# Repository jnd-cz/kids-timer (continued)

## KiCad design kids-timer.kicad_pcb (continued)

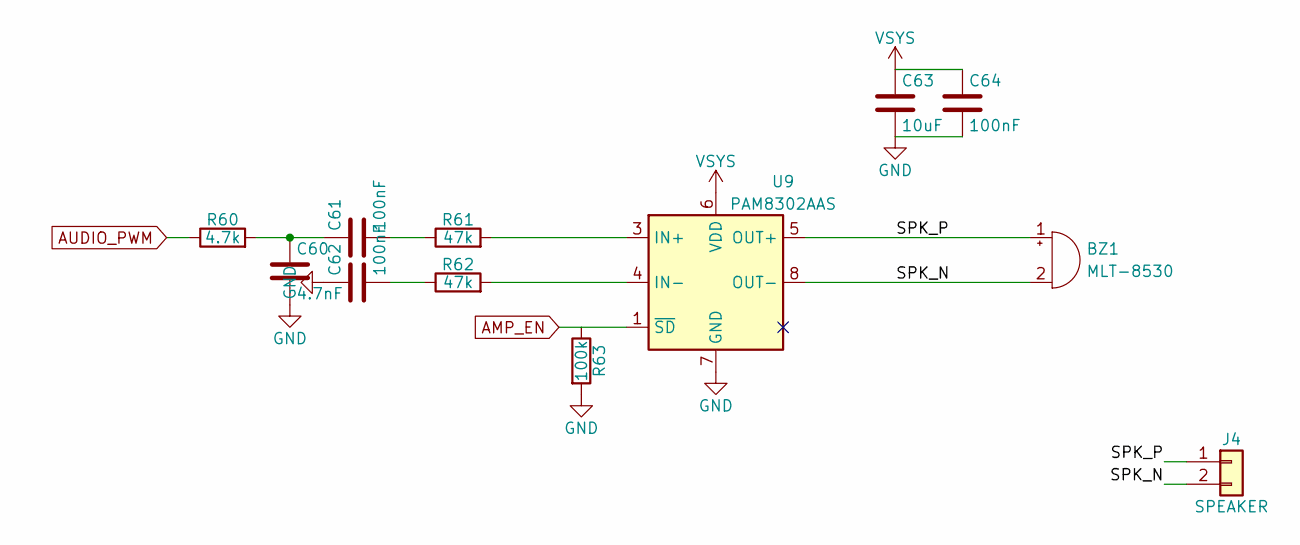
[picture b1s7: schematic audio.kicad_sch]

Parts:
BZ1: MLT-8530; Buzzer_HNDZ_MLT-8530_8.5x8.5mm; MPN MLT-8530; LCSC C94599
C60: 4.7nF; C_0402_1005Metric; LCSC C1538
C61, C62, C64: 100nF; C_0402_1005Metric; LCSC C1525
C63: 10uF; C_0805_2012Metric; LCSC C15850
J4: SPEAKER; JST_PH_S2B-PH-SM4-TB_1x02-1MP_P2.00mm_Horizontal; MPN S2B-PH-SM4-TB(LF)(SN); LCSC C295747
R60: 4.7k; R_0402_1005Metric; LCSC C25900
R61, R62: 47k; R_0402_1005Metric; LCSC C25792
R63: 100k; R_0402_1005Metric; LCSC C25741
U9: PAM8302AAS; MSOP-8_3x3mm_P0.65mm; MPN PAM8302AASCR; LCSC C113367

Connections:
/Audio/SPK_N: BZ1.2 (-), J4.2, U9.8 (OUT-)
/Audio/SPK_P: BZ1.1 (+), J4.1, U9.5 (OUT+)
AMP_EN: R63.1, U9.1 (~SD); also elsewhere on the board
AUDIO_PWM: R60.1; also elsewhere on the board
unnamed: C60.1, C61.1, R60.2
unnamed: C61.2, R61.1
unnamed: C62.2, R62.1
unnamed: R61.2, U9.3 (IN+)
unnamed: R62.2, U9.4 (IN-)
VSYS: C63.1, C64.1, U9.6 (VDD); also elsewhere on the board

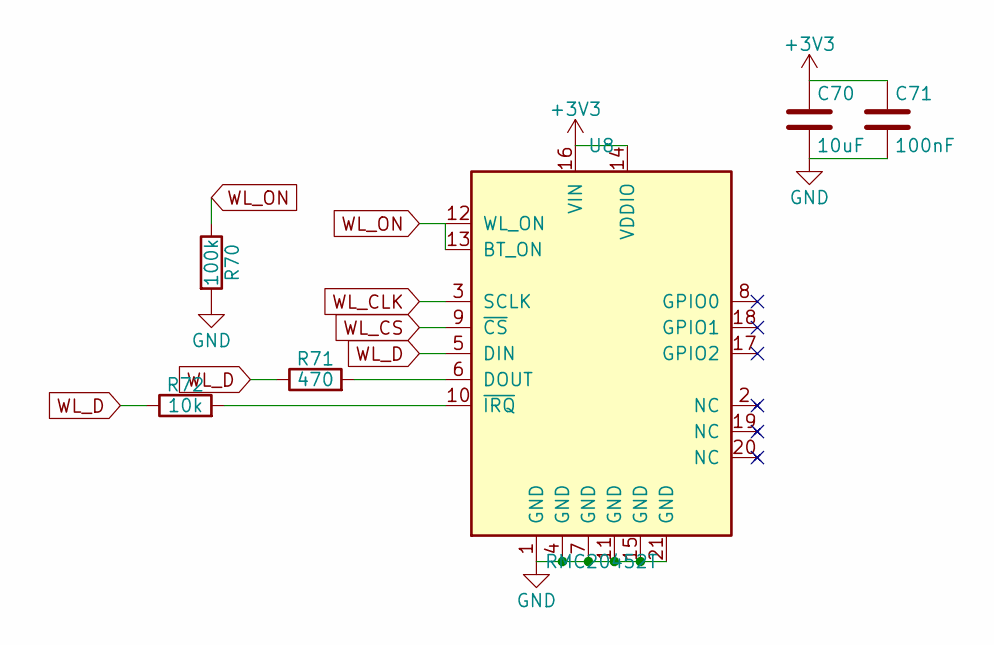
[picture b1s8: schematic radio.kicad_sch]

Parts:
C70: 10uF; C_0805_2012Metric; LCSC C15850
C71: 100nF; C_0402_1005Metric; LCSC C1525
R70: 100k; R_0402_1005Metric; LCSC C25741
R71: 470; R_0402_1005Metric; LCSC C25117
R72: 10k; R_0402_1005Metric; LCSC C25744
U8: RMC20452T; RaspberryPi_RM2_14.5x16.5mm; MPN RMC20452T; LCSC C49451547

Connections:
+3V3: C70.1, C71.1, U8.14 (VDDIO), U8.16 (VIN); also elsewhere on the board
unnamed: R71.2, U8.6 (DOUT)
unnamed: R72.2, U8.10 (~IRQ)
WL_CLK: U8.3 (SCLK); also elsewhere on the board
WL_CS: U8.9 (~CS); also elsewhere on the board
WL_D: R71.1, R72.1, U8.5 (DIN); also elsewhere on the board
WL_ON: R70.1, U8.12 (WL_ON), U8.13 (BT_ON); also elsewhere on the board

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
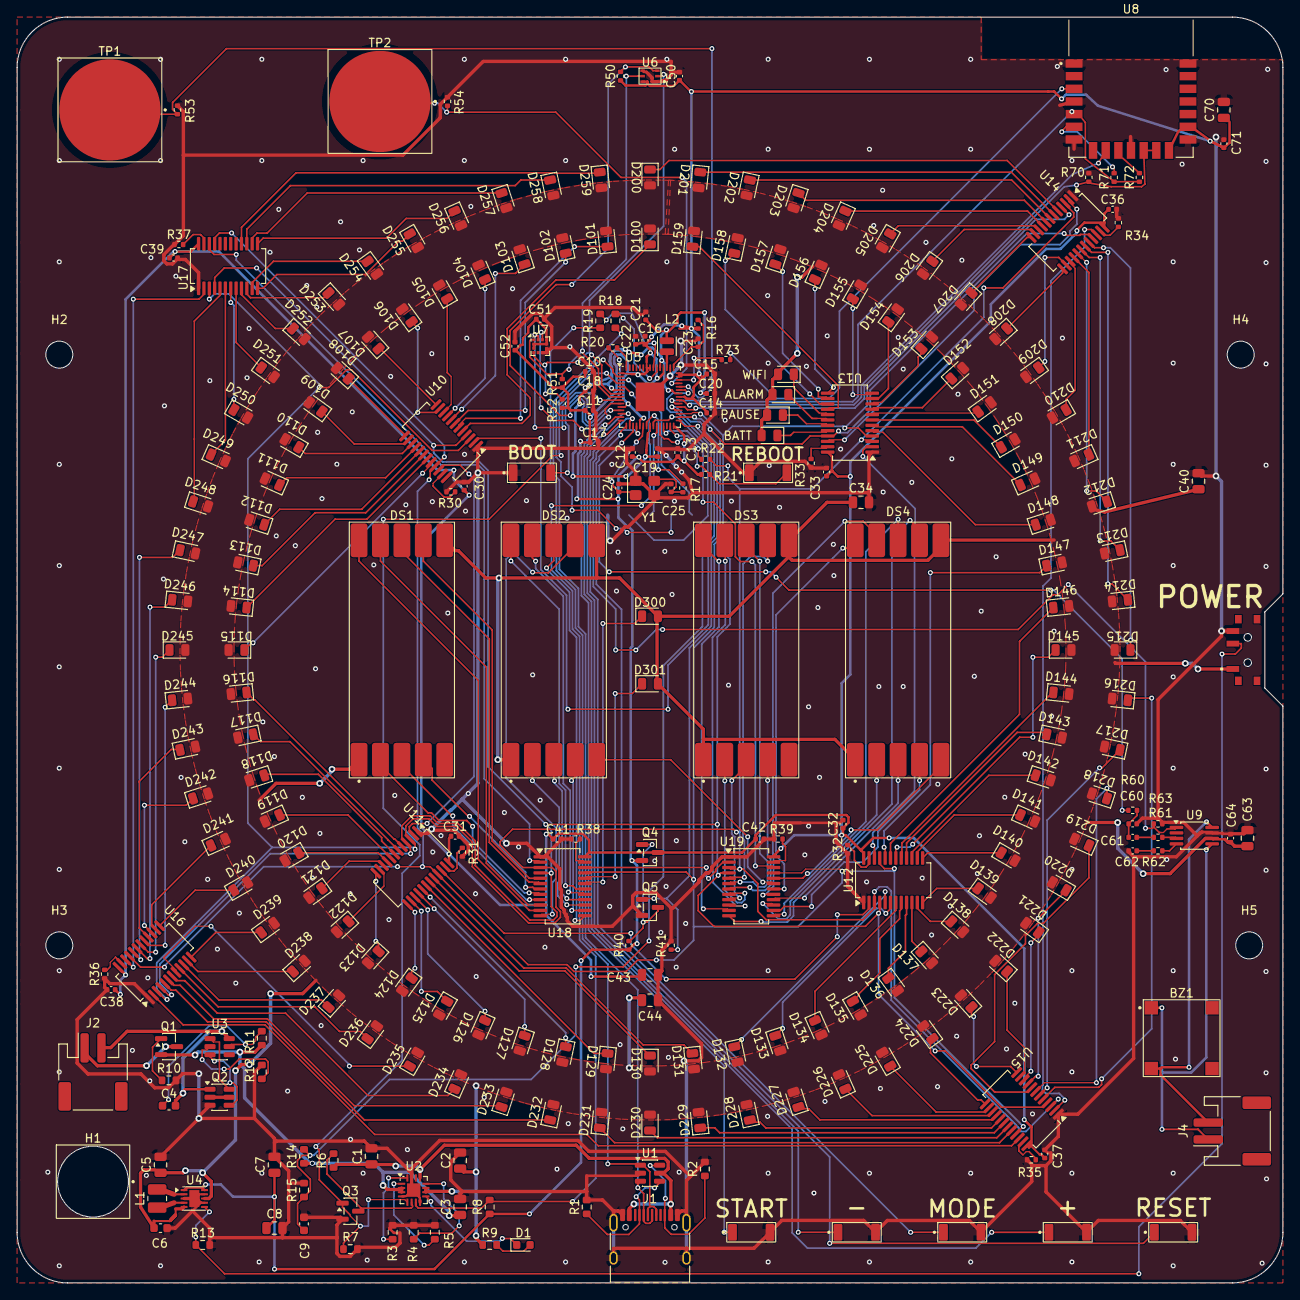
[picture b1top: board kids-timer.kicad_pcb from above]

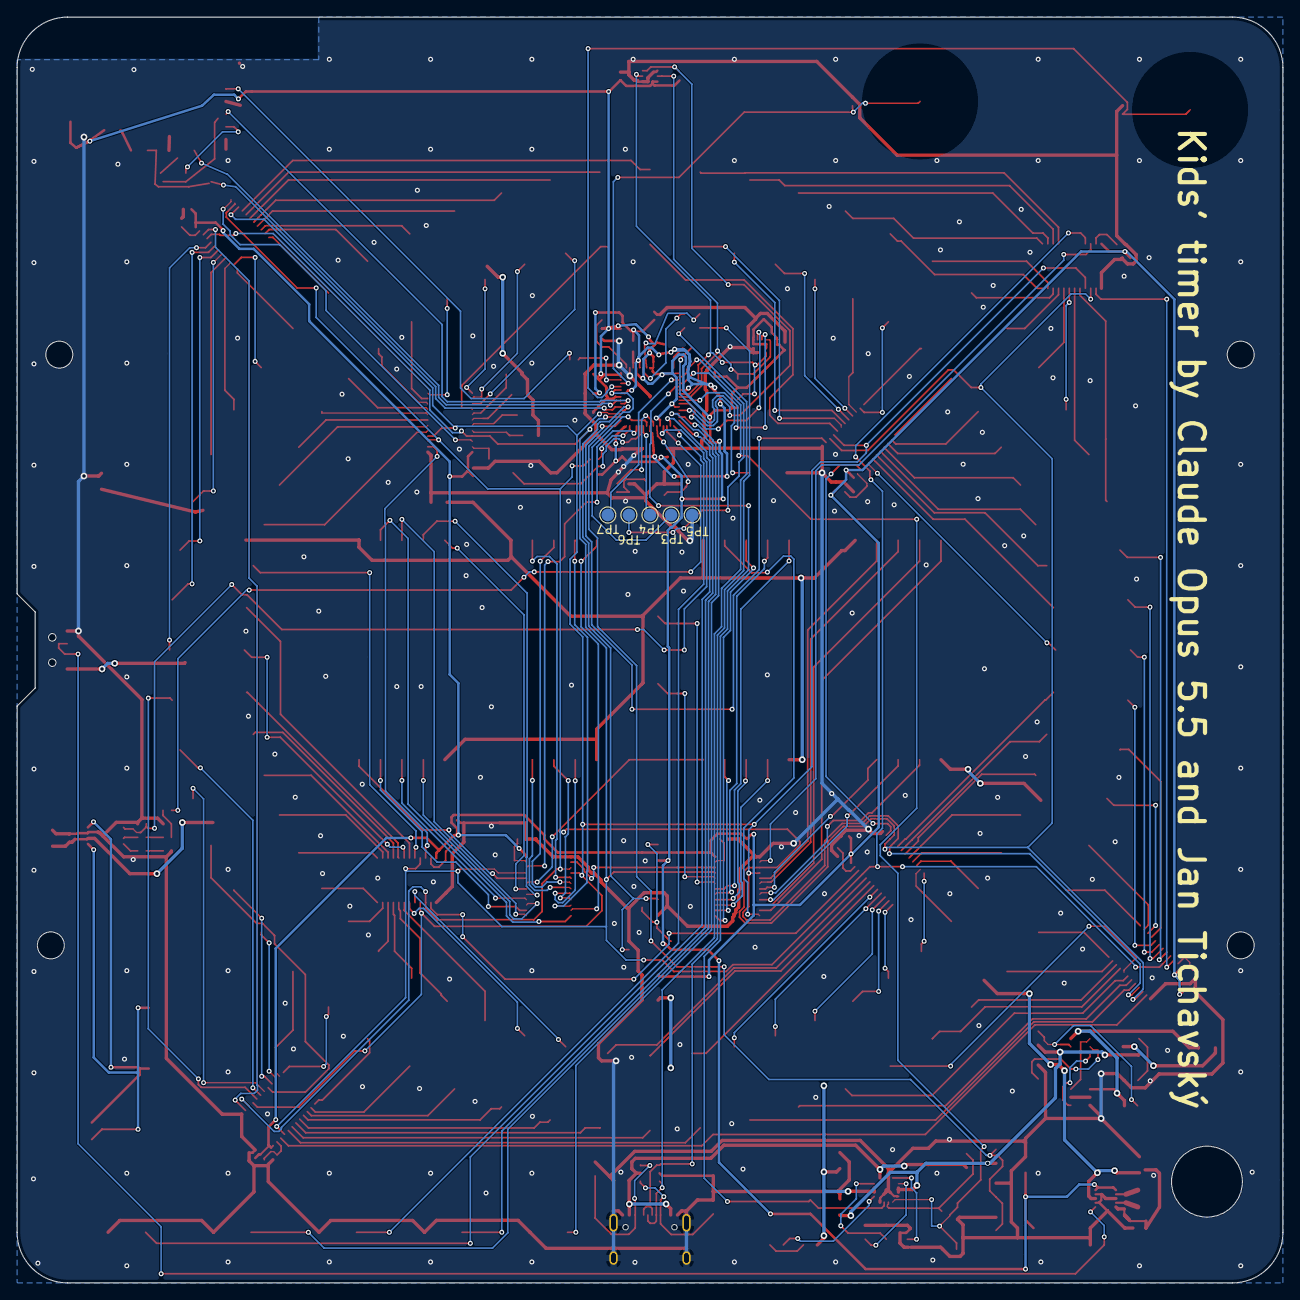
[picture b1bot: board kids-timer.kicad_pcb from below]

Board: 2 copper layers, 150.0 x 150.0 mm, 278 parts (5 on the bottom side), 256 nets.

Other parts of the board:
H1: WirePassThrough_8.4mm
H2, H3, H4, H5: MountingHole_3.2mm_M3

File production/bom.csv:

Designator,Footprint,Quantity,Value,LCSC Part #
BZ1,Buzzer_HNDZ_MLT-8530_8.5x8.5mm,1,MLT-8530,C94599
C1,0805,1,4.7uF,C1779
"C10, C11, C12, C13, C14, C15, C16, C17, C18, C19, C20, C30, C31, C32, C33, C36, C37, C38, C39, C41, C42, C50, C51, C61, C62, C64, C71",0402,27,100nF,C1525
"C2, C3, C43, C5, C63, C7, C70, C8",0805,8,10uF,C15850
"C21, C22, C23, C52",0402,4,4.7uF,C23733
"C24, C25",0402,2,33pF,C1562
"C34, C40, C44",0805,3,22uF,C45783
"C4, C6, C9",0603,3,100nF,C14663
C60,0402,1,4.7nF,C1538
D1,0603,1,CHG,C2286
"D100, D101, D102, D103, D104, D105, D106, D107, D108, D109, D110, D111, D112, D113, D114, D115, D116, D117, D118, D119, D120, D121, D122, D123, D124, D125, D126, D127, D128, D129, D130, D131, D132, D133, D134, D135, D136, D137, D138, D139, D140, D141, D142, D143, D144, D145, D146, D147, D148, D149, D150, D151, D152, D153, D154, D155, D156, D157, D158, D159",0805,60,GREEN,C2297
"D160, D161, D162, D163",0805,4,YELLOW,C2296
"D200, D201, D202, D203, D204, D205, D206, D207, D208, D209, D210, D211, D212, D213, D214, D215, D216, D217, D218, D219, D220, D221, D222, D223, D224, D225, D226, D227, D228, D229, D230, D231, D232, D233, D234, D235, D236, D237, D238, D239, D240, D241, D242, D243, D244, D245, D246, D247, D248, D249, D250, D251, D252, D253, D254, D255, D256, D257, D258, D259",0805,60,RED,C84256
"D300, D301",0805,2,WHITE,C34499
"DS1, DS2, DS3, DS4",GS8011_SMD_16.8x28mm,4,GS8011AW-G,C22462707
J1,USB_C_Receptacle_HRO_TYPE-C-31-M-12,1,USB-C,C165948
J2,JST_PH_S2B-PH-SM4-TB_1x02-1MP_P2.00mm_Horizontal,1,LiPo JST-PH,C295747
J4,JST_PH_S2B-PH-SM4-TB_1x02-1MP_P2.00mm_Horizontal,1,SPEAKER,C295747
L1,1008,1,1.5uH,C98349
L2,L_Changjiang_FTC201612S,1,3.3uH,C41405891
"Q1, Q4",SOT-23,2,AO3401A,C15127
Q2,SOT-23-6,1,HJ8205,C20069150
"Q3, Q5",SOT-23,2,2N7002,C8545
"R1, R2",0603,2,5.1k,C23186
"R10, R6, R7, R8",0603,4,100k,C25803
R11,0603,1,100,C22775
"R12, R3",0603,2,1k,C21190
R13,0603,1,1M,C22935
"R14, R15",0603,2,220k,C22961
"R16, R22, R73",0402,3,33,C25105
"R17, R20",0402,2,1k,C11702
"R18, R19",0603,2,27,C25190
"R21, R50, R72",0402,3,10k,C25744
"R30, R31, R32, R33, R34, R35, R36, R37",0402,8,3.3k,C25890
"R38, R39",0402,2,2k,C4109
R4,0603,1,1.2k,C22765
"R40, R41, R63, R70",0402,4,100k,C25741
R5,0603,1,10k,C25804
"R51, R52, R60",0402,3,4.7k,C25900
"R53, R54",0402,2,1M,C26083
"R61, R62",0402,2,47k,C25792
R71,0402,1,470,C25117
R9,0603,1,1.5k,C22843
SW1,SW_SPDT_MSK12C02_EdgeNotch,1,MSK12C02,C22435661
SW2,SW_SPST_XUNPU_TS-1088_3.9x3mm,1,BOOTSEL,C720477
SW3,SW_SPST_XUNPU_TS-1088_3.9x3mm,1,RESET,C720477
SW4,SW_SPST_XUNPU_TS-1088_3.9x3mm,1,BTN1,C720477
SW5,SW_SPST_XUNPU_TS-1088_3.9x3mm,1,BTN2,C720477
SW6,SW_SPST_XUNPU_TS-1088_3.9x3mm,1,BTN3,C720477
SW7,SW_SPST_XUNPU_TS-1088_3.9x3mm,1,BTN4,C720477
SW8,SW_SPST_XUNPU_TS-1088_3.9x3mm,1,BTN5,C720477
U1,SOT-23-6,1,SRV05-4,C85364
"U10, U11, U12, U13, U14, U15, U16, U17, U18, U19",QSOP-24_3.9x8.7mm_P0.635mm,10,SM16206S,C121618
U2,VQFN-16-1EP_3x3mm_P0.5mm_EP1.6x1.6mm,1,BQ24073RGT,C15220
U3,SOT-23-6,1,DW01A,C42380662
U4,WSON-10-1EP_2.5x2.5mm_P0.5mm_EP1.2x2mm,1,TPS63031DSK,C15516
U5,QFN-60-1EP_7x7mm_P0.4mm_EP3.4x3.4mm,1,RP2354A,C41378174
U6,Vishay_VEML6030_2x2mm,1,VEML6030,C132182
U7,LGA-12_2x2mm_P0.5mm,1,STK8328-C,C49230199
U8,RaspberryPi_RM2_14.5x16.5mm,1,RMC20452T,C49451547
U9,MSOP-8_3x3mm_P0.65mm,1,PAM8302AAS,C113367
Y1,Crystal_SMD_3225-4Pin_3.2x2.5mm,1,12MHz 20pF,C9002
